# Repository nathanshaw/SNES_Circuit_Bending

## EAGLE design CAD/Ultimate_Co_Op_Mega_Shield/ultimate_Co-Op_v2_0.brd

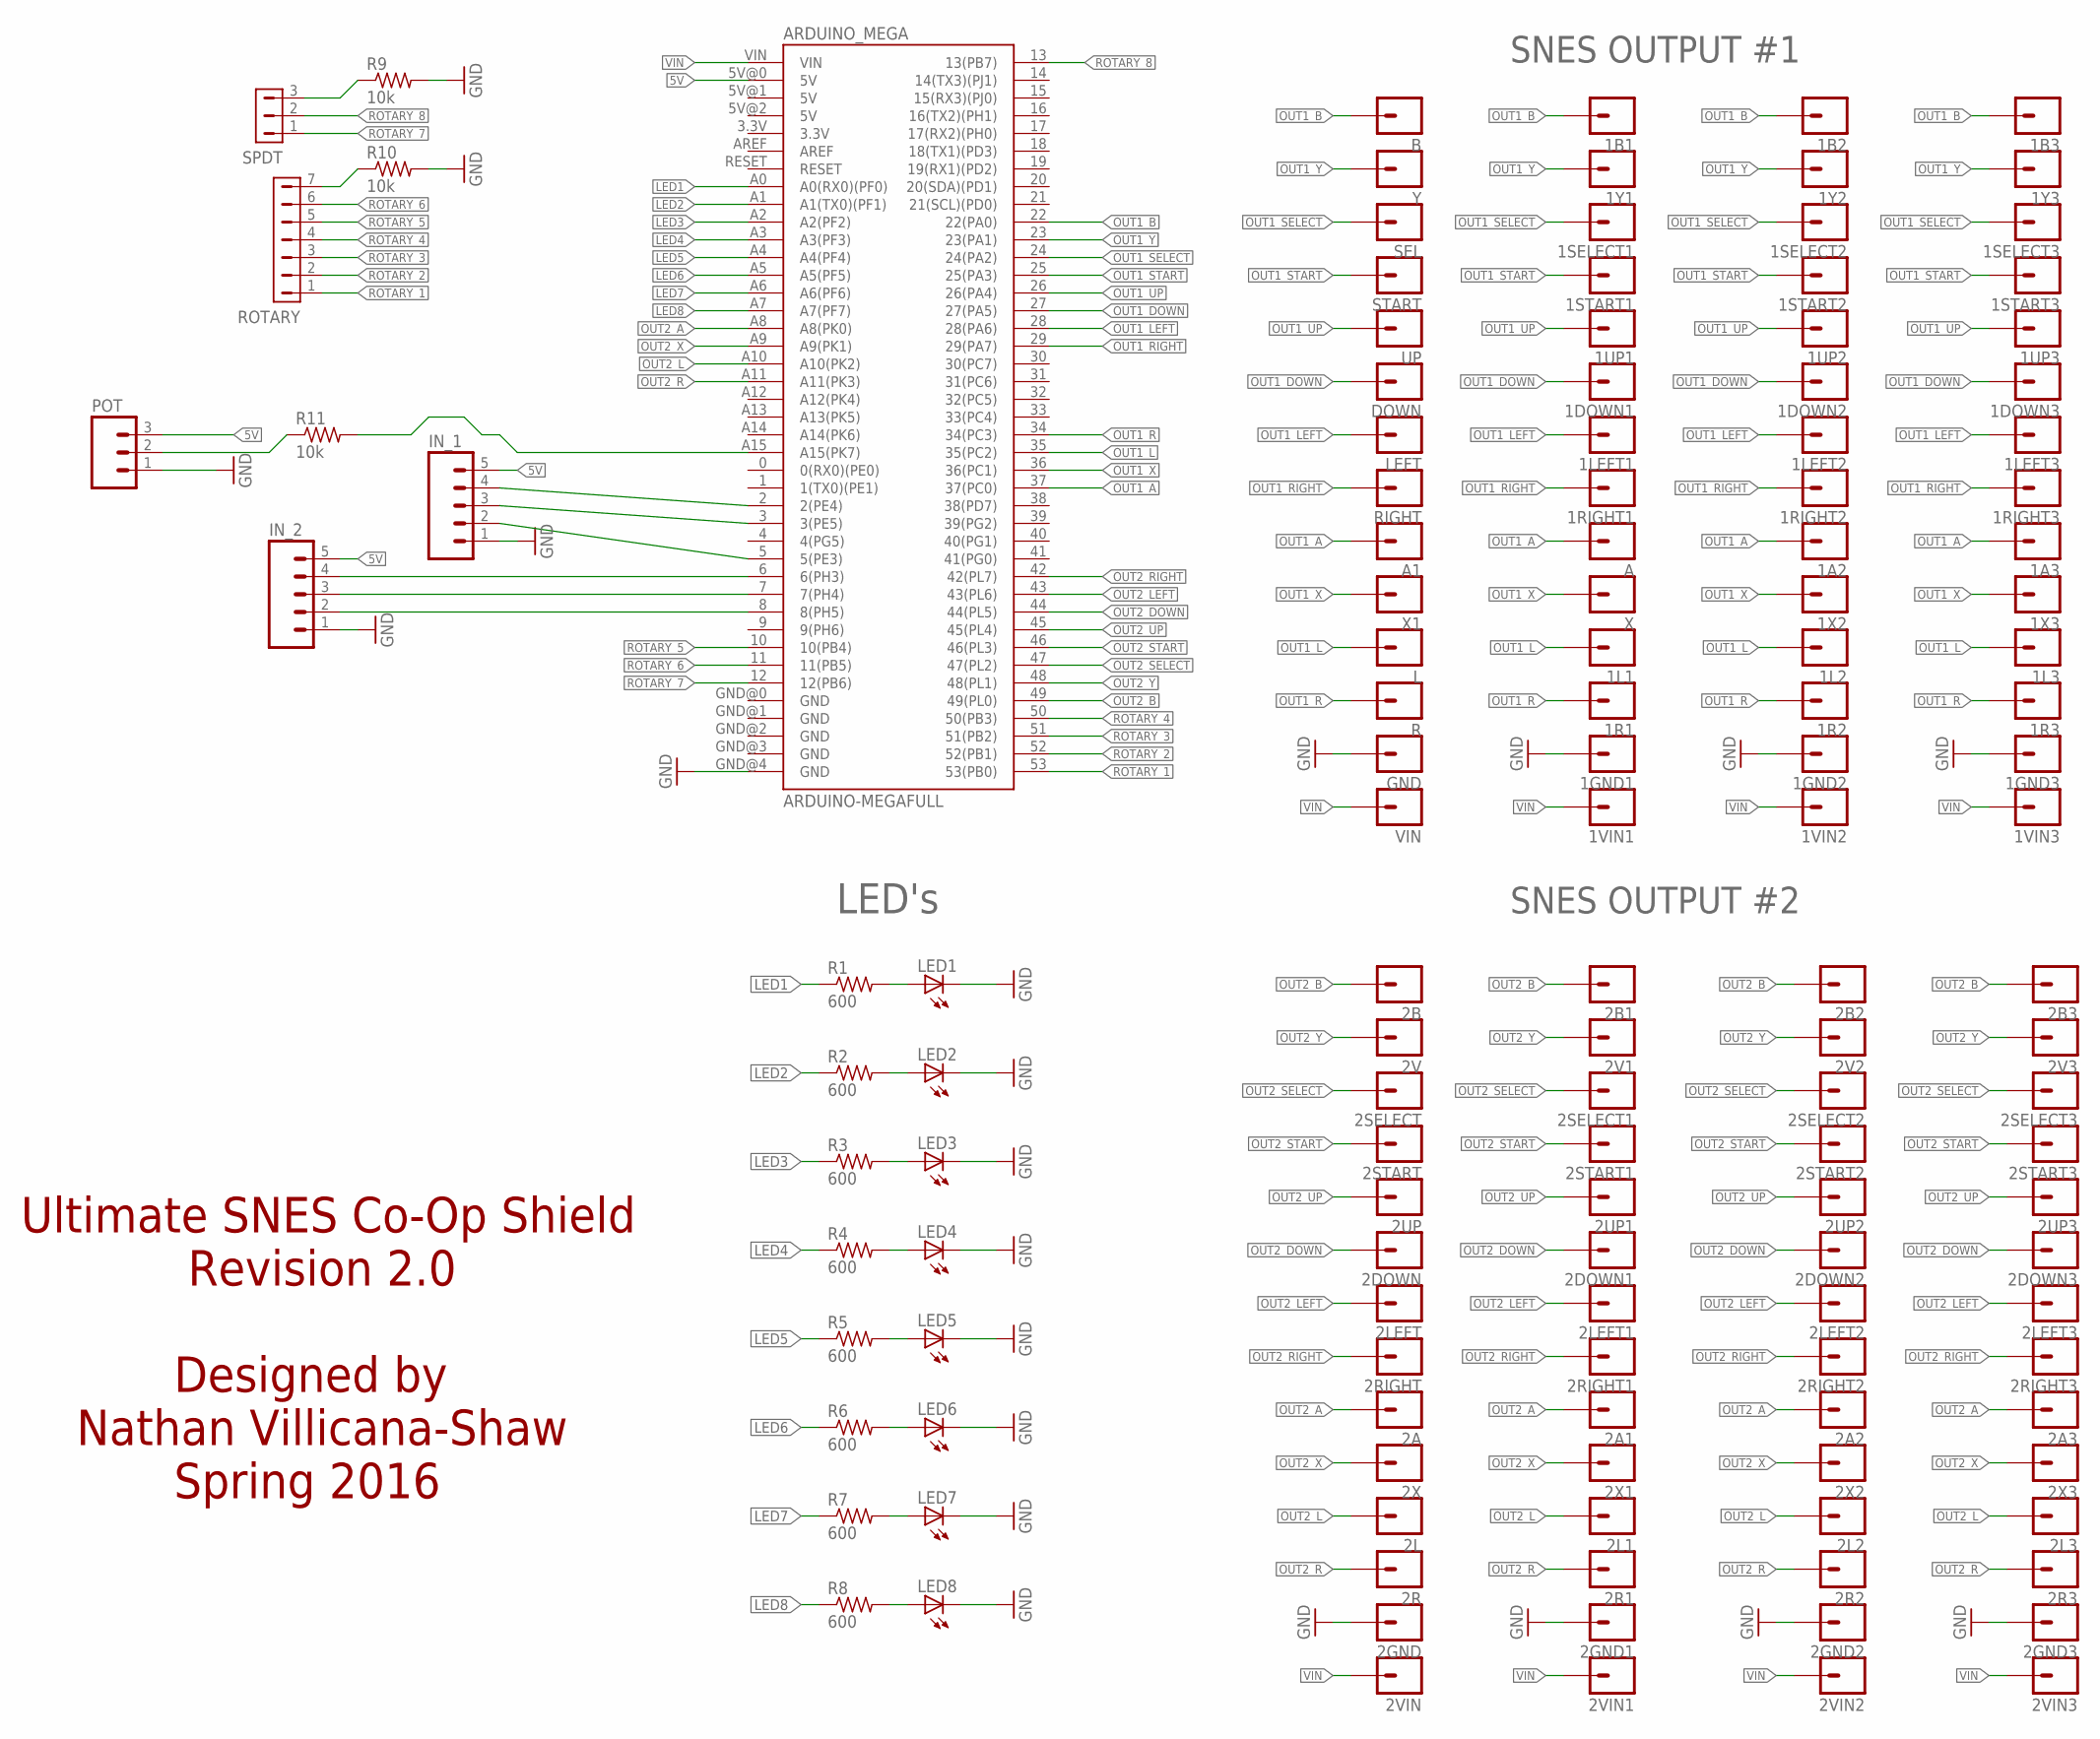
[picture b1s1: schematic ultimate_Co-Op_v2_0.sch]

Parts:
1A2, 1A3, 1B1, 1B2, 1B3, 1DOWN1, 1DOWN2, 1DOWN3, 1GND1, 1GND2, 1GND3, 1L1, 1L2, 1L3, 1LEFT1, 1LEFT2, 1LEFT3, 1R1, 1R2, 1R3, 1RIGHT1, 1RIGHT2, 1RIGHT3, 1SELECT1, 1SELECT2, 1SELECT3, 1START1, 1START2, 1START3, 1UP1, 1UP2, 1UP3, 1VIN1, 1VIN2, 1VIN3, 1X2, 1X3, 1Y1, 1Y2, 1Y3, 2A, 2A1, 2A2, 2A3, 2B, 2B1, 2B2, 2B3, 2DOWN, 2DOWN1, 2DOWN2, 2DOWN3, 2GND, 2GND1, 2GND2, 2GND3, 2L, 2L1, 2L2, 2L3, 2LEFT, 2LEFT1, 2LEFT2, 2LEFT3, 2R, 2R1, 2R2, 2R3, 2RIGHT, 2RIGHT1, 2RIGHT2, 2RIGHT3, 2SELECT, 2SELECT1, 2SELECT2, 2SELECT3, 2START, 2START1, 2START2, 2START3, 2UP, 2UP1, 2UP2, 2UP3, 2V, 2V1, 2V2, 2V3, 2VIN, 2VIN1, 2VIN2, 2VIN3, 2X, 2X1, 2X2, 2X3: M01PTH; 1X01
A, A1: M01PTH; 1X01
ARDUINO_MEGA: ARDUINO-MEGAFULL; ARDUINO_MEGA
B: M01PTH; 1X01
DOWN: M01PTH; 1X01
GND: M01PTH; 1X01
IN_1, IN_2: M05PTH; 1X05
L: M01PTH; 1X01
LED1, LED2, LED3, LED4, LED5, LED6, LED7, LED8: LED5MM
LEFT: M01PTH; 1X01
POT: M03LONGPADS; 1X03_LONGPADS
R: M01PTH; 1X01
R1, R2, R3, R4, R5, R6, R7, R8: 600; 0204/7
R9, R10, R11: 10k; 0204/7
RIGHT: M01PTH; 1X01
ROTARY: HDR-1X7-MTE-100; MTE-100-7V
SEL: M01PTH; 1X01
SPDT: HDR-1X3-MTA-100; MTA-100-3V
START: M01PTH; 1X01
UP: M01PTH; 1X01
VIN: M01PTH; 1X01
X, X1: M01PTH; 1X01
Y: M01PTH; 1X01

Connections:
5V: ARDUINO_MEGA.5V@0 (5V), IN_1.5, IN_2.5, POT.3
GND: 1GND1.1, 1GND2.1, 1GND3.1, 2GND.1, 2GND1.1, 2GND2.1, 2GND3.1, ARDUINO_MEGA.GND@4 (GND), GND.1, IN_1.1, IN_2.1, LED1.K (C), LED2.K (C), LED3.K (C), LED4.K (C), LED5.K (C), LED6.K (C), LED7.K (C), LED8.K (C), POT.1, R9.2, R10.2
LED1: ARDUINO_MEGA.A0 (A0(RX0)(PF0)), R1.1
LED2: ARDUINO_MEGA.A1 (A1(TX0)(PF1)), R2.1
LED3: ARDUINO_MEGA.A2 (A2(PF2)), R3.1
LED4: ARDUINO_MEGA.A3 (A3(PF3)), R4.1
LED5: ARDUINO_MEGA.A4 (A4(PF4)), R5.1
LED6: ARDUINO_MEGA.A5 (A5(PF5)), R6.1
LED7: ARDUINO_MEGA.A6 (A6(PF6)), R7.1
LED8: ARDUINO_MEGA.A7 (A7(PF7)), R8.1
LSJDFKS: ARDUINO_MEGA.6 (6(PH3)), IN_2.4
unnamed: LED1.A, R1.2
unnamed: LED2.A, R2.2
unnamed: LED3.A, R3.2
unnamed: LED4.A, R4.2
unnamed: LED5.A, R5.2
unnamed: LED6.A, R6.2
unnamed: LED7.A, R7.2
unnamed: LED8.A, R8.2
unnamed: ARDUINO_MEGA.2 (2(PE4)), IN_1.4
unnamed: ARDUINO_MEGA.3 (3(PE5)), IN_1.3
unnamed: ARDUINO_MEGA.5 (5(PE3)), IN_1.2
unnamed: ARDUINO_MEGA.A15 (A15(PK7)), R11.2
unnamed: ARDUINO_MEGA.7 (7(PH4)), IN_2.3
unnamed: ARDUINO_MEGA.8 (8(PH5)), IN_2.2
unnamed: POT.2, R11.1
OIJNENLK: R9.1, SPDT.3
OIJNENLK1: R10.1, ROTARY.7
OUT1_A: 1A2.1, 1A3.1, A.1, A1.1, ARDUINO_MEGA.37 (37(PC0))
OUT1_B: 1B1.1, 1B2.1, 1B3.1, ARDUINO_MEGA.22 (22(PA0)), B.1
OUT1_DOWN: 1DOWN1.1, 1DOWN2.1, 1DOWN3.1, ARDUINO_MEGA.27 (27(PA5)), DOWN.1
OUT1_L: 1L1.1, 1L2.1, 1L3.1, ARDUINO_MEGA.35 (35(PC2)), L.1
OUT1_LEFT: 1LEFT1.1, 1LEFT2.1, 1LEFT3.1, ARDUINO_MEGA.28 (28(PA6)), LEFT.1
OUT1_R: 1R1.1, 1R2.1, 1R3.1, ARDUINO_MEGA.34 (34(PC3)), R.1
OUT1_RIGHT: 1RIGHT1.1, 1RIGHT2.1, 1RIGHT3.1, ARDUINO_MEGA.29 (29(PA7)), RIGHT.1
OUT1_SELECT: 1SELECT1.1, 1SELECT2.1, 1SELECT3.1, ARDUINO_MEGA.24 (24(PA2)), SEL.1
OUT1_START: 1START1.1, 1START2.1, 1START3.1, ARDUINO_MEGA.25 (25(PA3)), START.1
OUT1_UP: 1UP1.1, 1UP2.1, 1UP3.1, ARDUINO_MEGA.26 (26(PA4)), UP.1
OUT1_X: 1X2.1, 1X3.1, ARDUINO_MEGA.36 (36(PC1)), X.1, X1.1
OUT1_Y: 1Y1.1, 1Y2.1, 1Y3.1, ARDUINO_MEGA.23 (23(PA1)), Y.1
OUT2_A: 2A.1, 2A1.1, 2A2.1, 2A3.1, ARDUINO_MEGA.A8 (A8(PK0))
OUT2_B: 2B.1, 2B1.1, 2B2.1, 2B3.1, ARDUINO_MEGA.49 (49(PL0))
OUT2_DOWN: 2DOWN.1, 2DOWN1.1, 2DOWN2.1, 2DOWN3.1, ARDUINO_MEGA.44 (44(PL5))
OUT2_L: 2L.1, 2L1.1, 2L2.1, 2L3.1, ARDUINO_MEGA.A10 (A10(PK2))
OUT2_LEFT: 2LEFT.1, 2LEFT1.1, 2LEFT2.1, 2LEFT3.1, ARDUINO_MEGA.43 (43(PL6))
OUT2_R: 2R.1, 2R1.1, 2R2.1, 2R3.1, ARDUINO_MEGA.A11 (A11(PK3))
OUT2_RIGHT: 2RIGHT.1, 2RIGHT1.1, 2RIGHT2.1, 2RIGHT3.1, ARDUINO_MEGA.42 (42(PL7))
OUT2_SELECT: 2SELECT.1, 2SELECT1.1, 2SELECT2.1, 2SELECT3.1, ARDUINO_MEGA.47 (47(PL2))
OUT2_START: 2START.1, 2START1.1, 2START2.1, 2START3.1, ARDUINO_MEGA.46 (46(PL3))
OUT2_UP: 2UP.1, 2UP1.1, 2UP2.1, 2UP3.1, ARDUINO_MEGA.45 (45(PL4))
OUT2_X: 2X.1, 2X1.1, 2X2.1, 2X3.1, ARDUINO_MEGA.A9 (A9(PK1))
OUT2_Y: 2V.1, 2V1.1, 2V2.1, 2V3.1, ARDUINO_MEGA.48 (48(PL1))
ROTARY_1: ARDUINO_MEGA.53 (53(PB0)), ROTARY.1
ROTARY_2: ARDUINO_MEGA.52 (52(PB1)), ROTARY.2
ROTARY_3: ARDUINO_MEGA.51 (51(PB2)), ROTARY.3
ROTARY_4: ARDUINO_MEGA.50 (50(PB3)), ROTARY.4
ROTARY_5: ARDUINO_MEGA.10 (10(PB4)), ROTARY.5
ROTARY_6: ARDUINO_MEGA.11 (11(PB5)), ROTARY.6
ROTARY_7: ARDUINO_MEGA.12 (12(PB6)), SPDT.1
ROTARY_8: ARDUINO_MEGA.13 (13(PB7)), SPDT.2
VIN: 1VIN1.1, 1VIN2.1, 1VIN3.1, 2VIN.1, 2VIN1.1, 2VIN2.1, 2VIN3.1, ARDUINO_MEGA.VIN, VIN.1

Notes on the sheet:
LED's
SNES OUTPUT #1
SNES OUTPUT #2
Ultimate SNES Co-Op Shield Revision 2.0 Designed by Nathan Villicana-Shaw Spring 2016

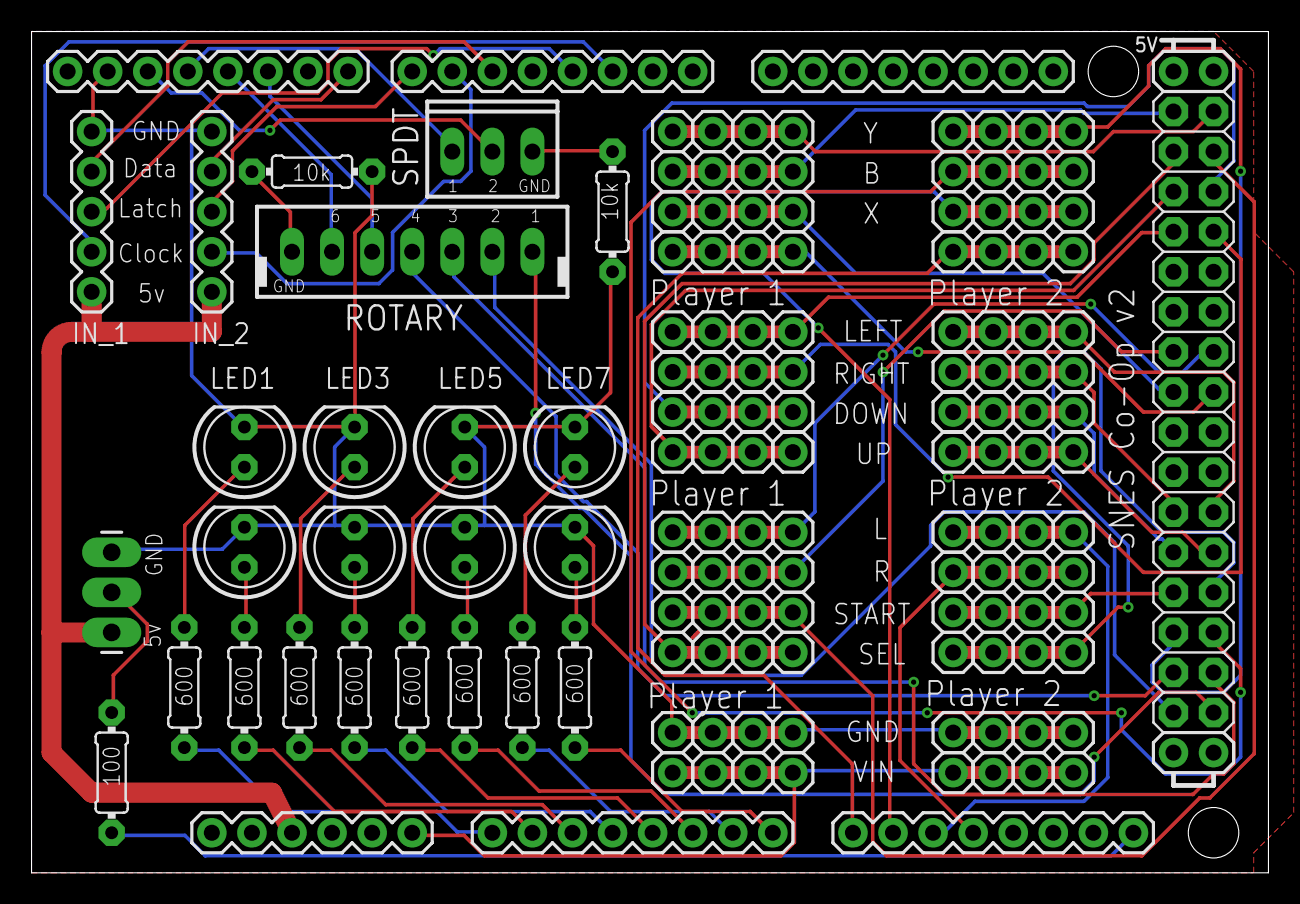
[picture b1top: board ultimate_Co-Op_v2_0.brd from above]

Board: 2 copper layers, 78.4 x 53.3 mm, 137 parts (0 on the bottom side), 61 nets.

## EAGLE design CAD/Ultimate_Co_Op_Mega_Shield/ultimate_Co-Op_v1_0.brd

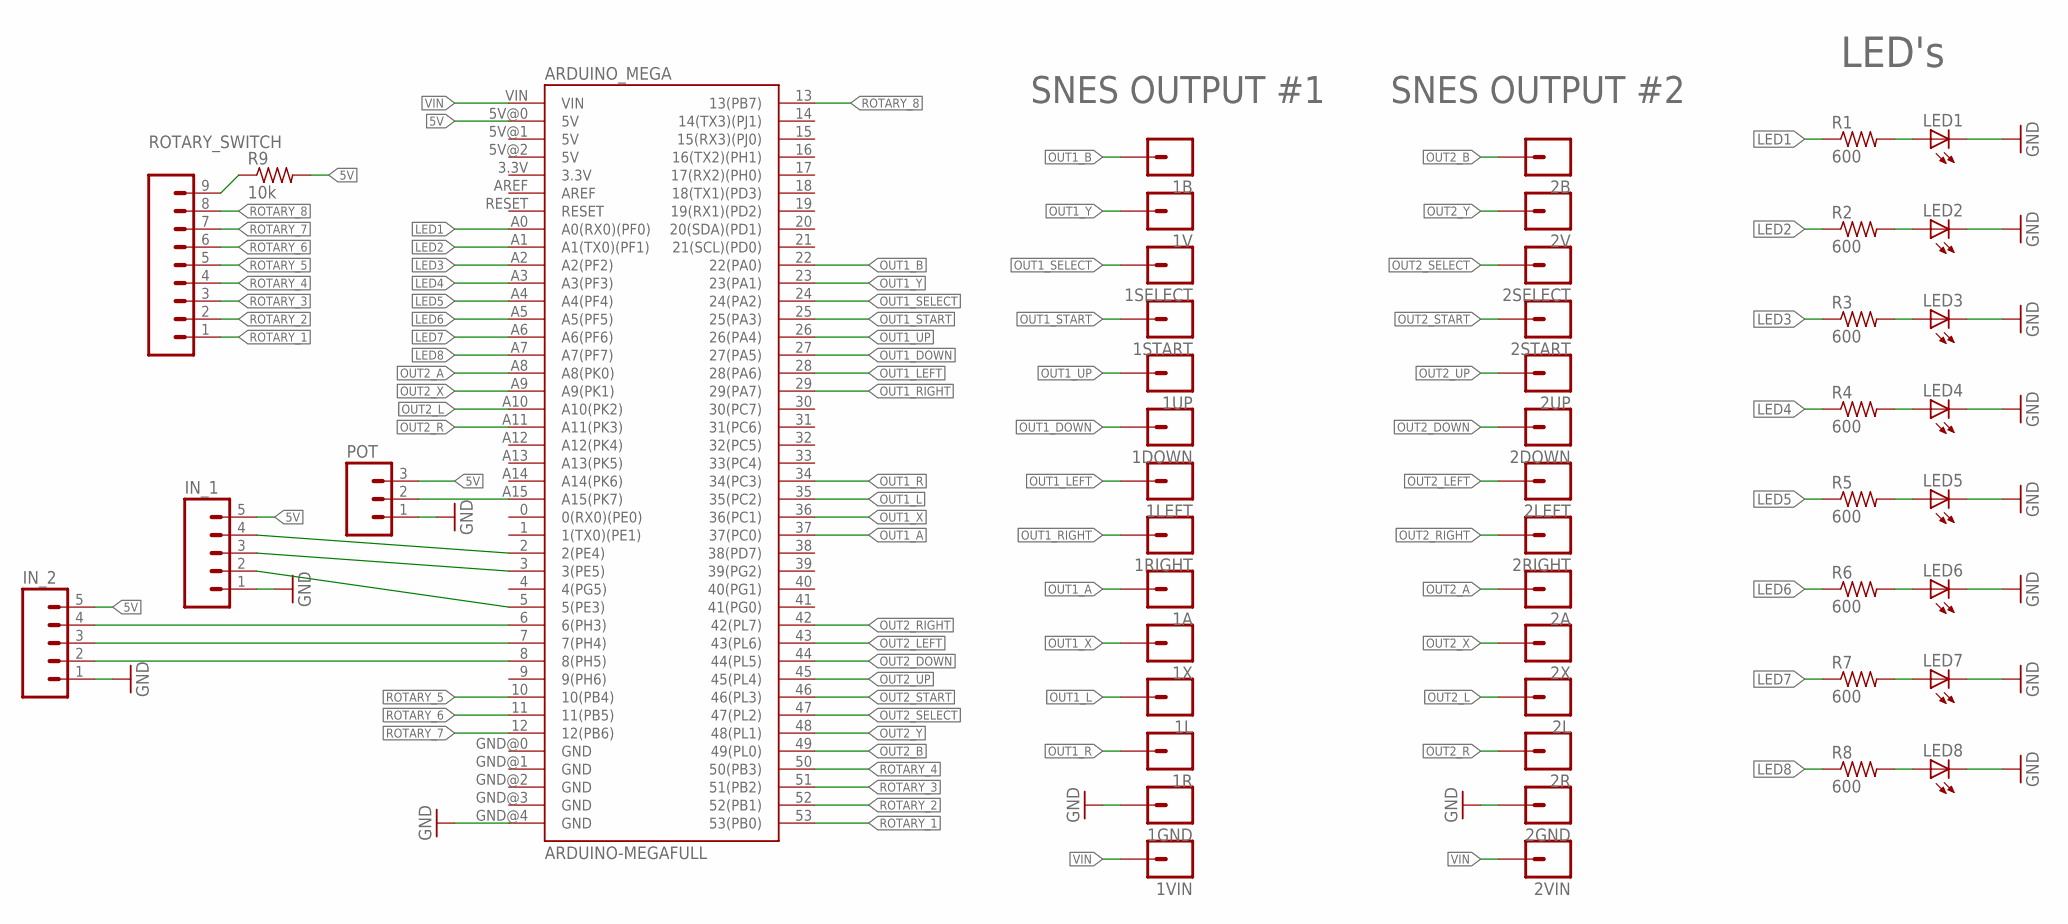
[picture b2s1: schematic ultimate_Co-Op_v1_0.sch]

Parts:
1A, 1B, 1DOWN, 1GND, 1L, 1LEFT, 1R, 1RIGHT, 1SELECT, 1START, 1UP, 1V, 1VIN, 1X, 2A, 2B, 2DOWN, 2GND, 2L, 2LEFT, 2R, 2RIGHT, 2SELECT, 2START, 2UP, 2V, 2VIN, 2X: M01PTH; 1X01
ARDUINO_MEGA: ARDUINO-MEGAFULL; ARDUINO_MEGA
IN_1, IN_2: M05PTH; 1X05
LED1, LED2, LED3, LED4, LED5, LED6, LED7, LED8: LED5MM
POT: M03LONGPADS; 1X03_LONGPADS
R1, R2, R3, R4, R5, R6, R7, R8: 600; 0204/7
R9: 10k; 0204/7
ROTARY_SWITCH: M09; 1X09

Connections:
5V: ARDUINO_MEGA.5V@0 (5V), IN_1.5, IN_2.5, POT.3, R9.2
GND: 1GND.1, 2GND.1, ARDUINO_MEGA.GND@4 (GND), IN_1.1, IN_2.1, LED1.K (C), LED2.K (C), LED3.K (C), LED4.K (C), LED5.K (C), LED6.K (C), LED7.K (C), LED8.K (C), POT.1
LED1: ARDUINO_MEGA.A0 (A0(RX0)(PF0)), R1.1
LED2: ARDUINO_MEGA.A1 (A1(TX0)(PF1)), R2.1
LED3: ARDUINO_MEGA.A2 (A2(PF2)), R3.1
LED4: ARDUINO_MEGA.A3 (A3(PF3)), R4.1
LED5: ARDUINO_MEGA.A4 (A4(PF4)), R5.1
LED6: ARDUINO_MEGA.A5 (A5(PF5)), R6.1
LED7: ARDUINO_MEGA.A6 (A6(PF6)), R7.1
LED8: ARDUINO_MEGA.A7 (A7(PF7)), R8.1
LSJDFKS: ARDUINO_MEGA.6 (6(PH3)), IN_2.4
unnamed: LED1.A, R1.2
unnamed: LED2.A, R2.2
unnamed: LED3.A, R3.2
unnamed: LED4.A, R4.2
unnamed: LED5.A, R5.2
unnamed: LED6.A, R6.2
unnamed: LED7.A, R7.2
unnamed: LED8.A, R8.2
unnamed: ARDUINO_MEGA.2 (2(PE4)), IN_1.4
unnamed: ARDUINO_MEGA.3 (3(PE5)), IN_1.3
unnamed: ARDUINO_MEGA.5 (5(PE3)), IN_1.2
unnamed: ARDUINO_MEGA.7 (7(PH4)), IN_2.3
unnamed: ARDUINO_MEGA.8 (8(PH5)), IN_2.2
OIJNENLK: R9.1, ROTARY_SWITCH.9
OUT1_A: 1A.1, ARDUINO_MEGA.37 (37(PC0))
OUT1_B: 1B.1, ARDUINO_MEGA.22 (22(PA0))
OUT1_DOWN: 1DOWN.1, ARDUINO_MEGA.27 (27(PA5))
OUT1_L: 1L.1, ARDUINO_MEGA.35 (35(PC2))
OUT1_LEFT: 1LEFT.1, ARDUINO_MEGA.28 (28(PA6))
OUT1_R: 1R.1, ARDUINO_MEGA.34 (34(PC3))
OUT1_RIGHT: 1RIGHT.1, ARDUINO_MEGA.29 (29(PA7))
OUT1_SELECT: 1SELECT.1, ARDUINO_MEGA.24 (24(PA2))
OUT1_START: 1START.1, ARDUINO_MEGA.25 (25(PA3))
OUT1_UP: 1UP.1, ARDUINO_MEGA.26 (26(PA4))
OUT1_X: 1X.1, ARDUINO_MEGA.36 (36(PC1))
OUT1_Y: 1V.1, ARDUINO_MEGA.23 (23(PA1))
OUT2_A: 2A.1, ARDUINO_MEGA.A8 (A8(PK0))
OUT2_B: 2B.1, ARDUINO_MEGA.49 (49(PL0))
OUT2_DOWN: 2DOWN.1, ARDUINO_MEGA.44 (44(PL5))
OUT2_L: 2L.1, ARDUINO_MEGA.A10 (A10(PK2))
OUT2_LEFT: 2LEFT.1, ARDUINO_MEGA.43 (43(PL6))
OUT2_R: 2R.1, ARDUINO_MEGA.A11 (A11(PK3))
OUT2_RIGHT: 2RIGHT.1, ARDUINO_MEGA.42 (42(PL7))
OUT2_SELECT: 2SELECT.1, ARDUINO_MEGA.47 (47(PL2))
OUT2_START: 2START.1, ARDUINO_MEGA.46 (46(PL3))
OUT2_UP: 2UP.1, ARDUINO_MEGA.45 (45(PL4))
OUT2_X: 2X.1, ARDUINO_MEGA.A9 (A9(PK1))
OUT2_Y: 2V.1, ARDUINO_MEGA.48 (48(PL1))
POT1: ARDUINO_MEGA.A15 (A15(PK7)), POT.2
ROTARY_1: ARDUINO_MEGA.53 (53(PB0)), ROTARY_SWITCH.1
ROTARY_2: ARDUINO_MEGA.52 (52(PB1)), ROTARY_SWITCH.2
ROTARY_3: ARDUINO_MEGA.51 (51(PB2)), ROTARY_SWITCH.3
ROTARY_4: ARDUINO_MEGA.50 (50(PB3)), ROTARY_SWITCH.4
ROTARY_5: ARDUINO_MEGA.10 (10(PB4)), ROTARY_SWITCH.5
ROTARY_6: ARDUINO_MEGA.11 (11(PB5)), ROTARY_SWITCH.6
ROTARY_7: ARDUINO_MEGA.12 (12(PB6)), ROTARY_SWITCH.7
ROTARY_8: ARDUINO_MEGA.13 (13(PB7)), ROTARY_SWITCH.8
VIN: 1VIN.1, 2VIN.1, ARDUINO_MEGA.VIN

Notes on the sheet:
LED's
SNES OUTPUT #1
SNES OUTPUT #2

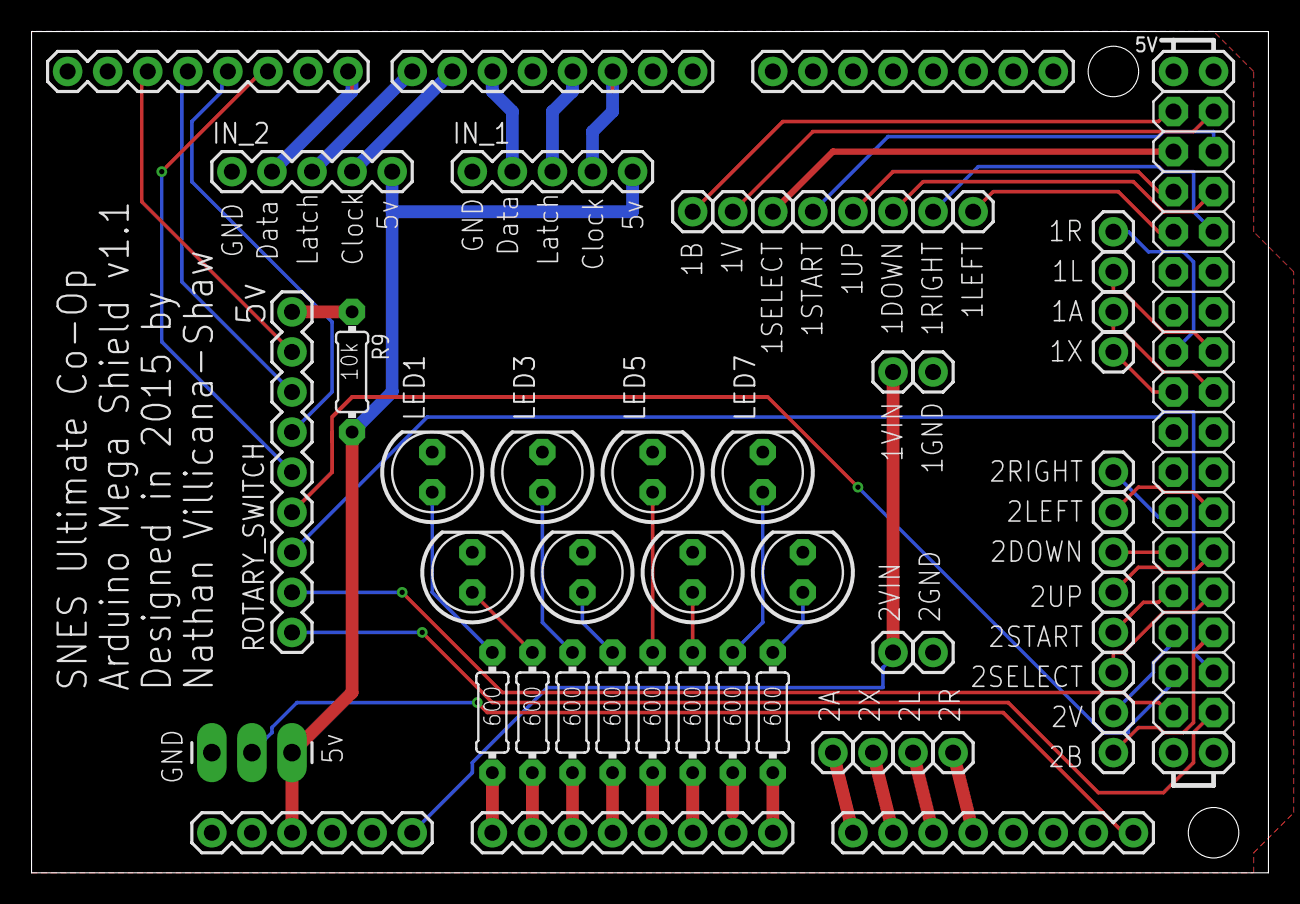
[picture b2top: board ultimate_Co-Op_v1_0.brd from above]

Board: 2 copper layers, 78.4 x 53.3 mm, 50 parts (0 on the bottom side), 59 nets.

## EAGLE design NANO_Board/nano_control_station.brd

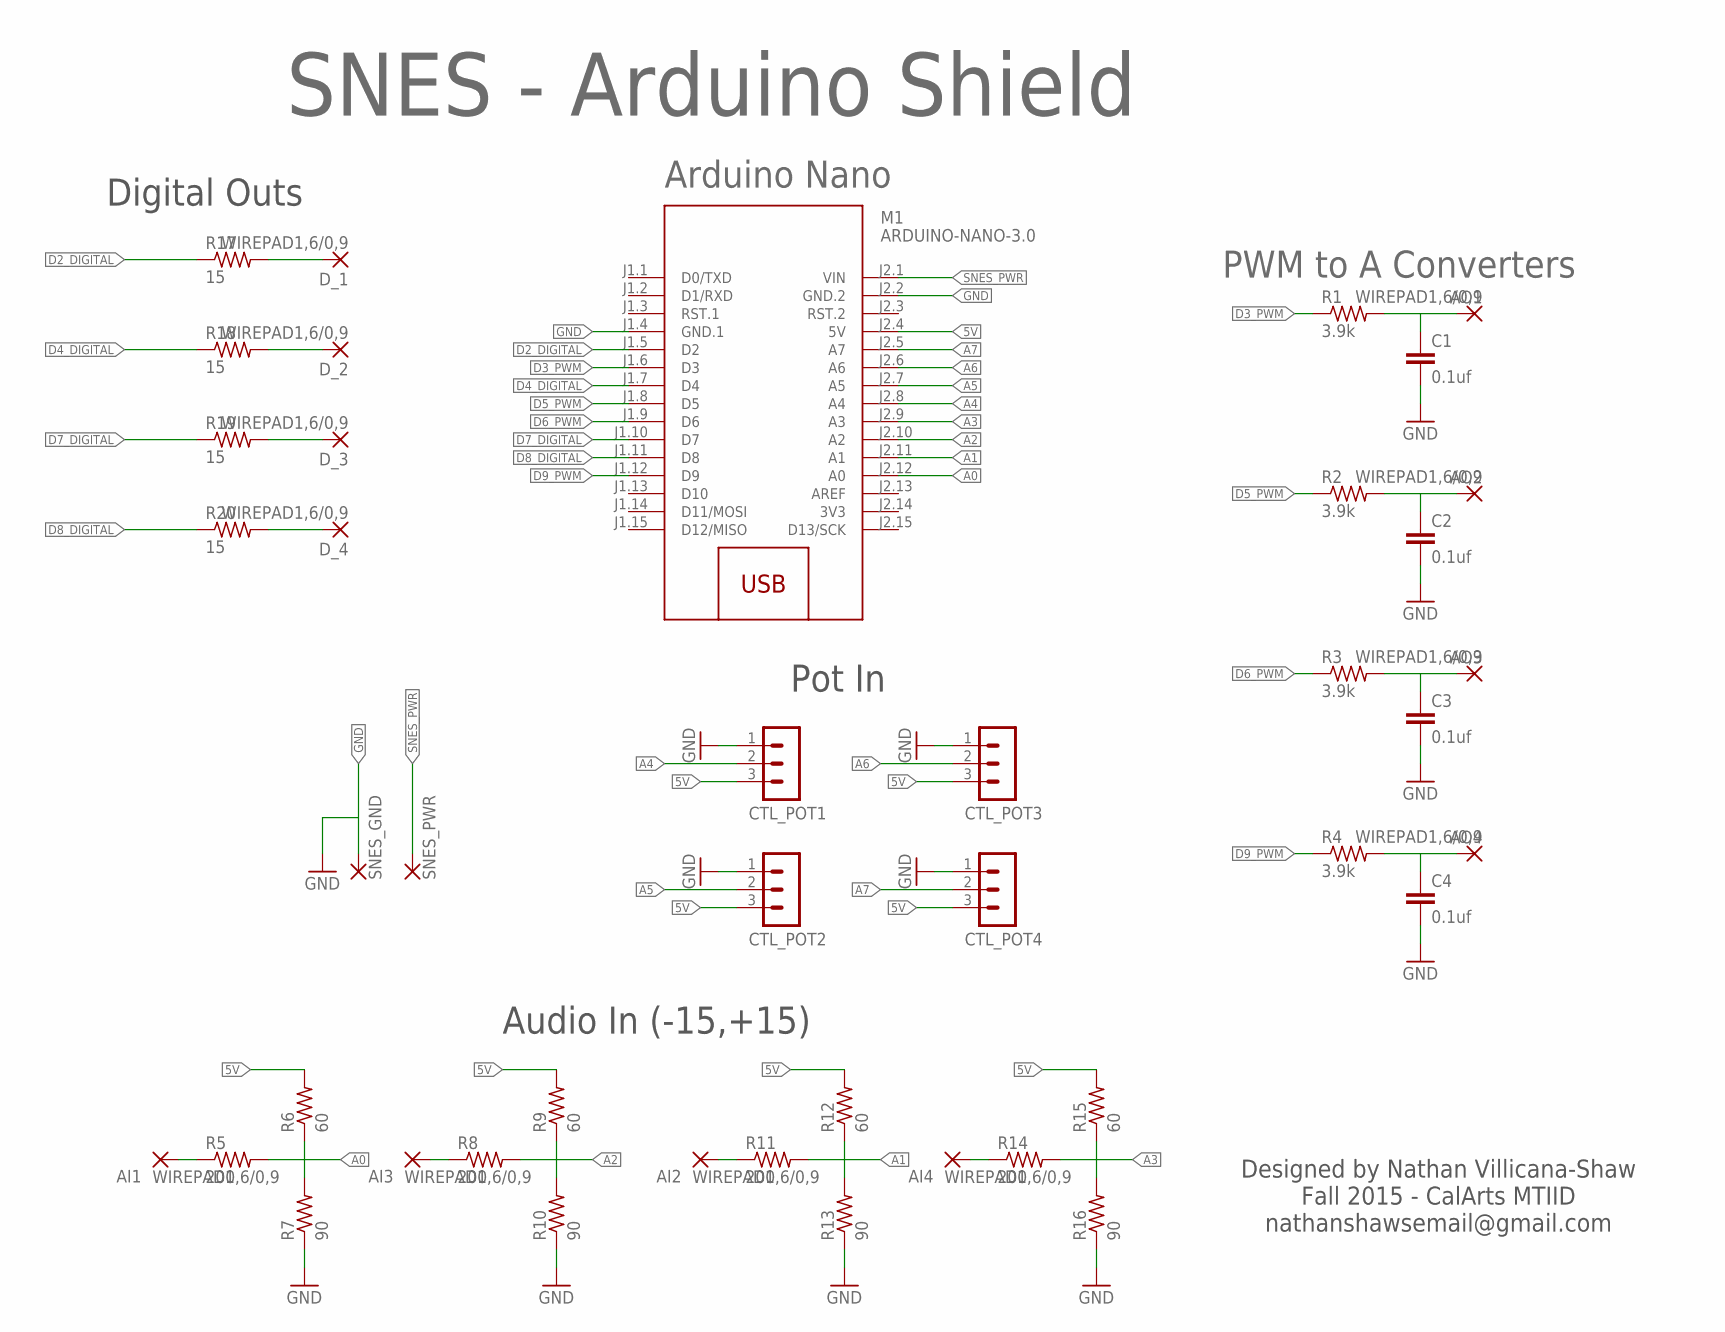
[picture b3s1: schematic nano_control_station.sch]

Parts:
AI1, AI2, AI3, AI4: WIREPAD1,6/0,9; 1,6/0,9
AO1, AO2, AO3, AO4: WIREPAD1,6/0,9; 1,6/0,9
C1, C2, C3, C4: 0.1uf; C2.5-2
CTL_POT1, CTL_POT2, CTL_POT3, CTL_POT4: MA03-1
D_1, D_2, D_3, D_4: WIREPAD1,6/0,9; 1,6/0,9
M1: ARDUINO-NANO-3.0
R1, R2, R3, R4: 3.9k; 0204/7
R5, R8, R11, R14: 200; 0204/7
R6, R9, R12, R15: 60; 0204/7
R7, R10, R13, R16: 90; 0204/7
R17, R18, R19, R20: 15; 0204/7
SNES_GND: 2,15/1,0
SNES_PWR: 2,15/1,0

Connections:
3V3: M1.J2.14 (3V3)
5V: CTL_POT1.3, CTL_POT2.3, CTL_POT3.3, CTL_POT4.3, M1.J2.4 (5V), R6.2, R9.2, R12.2, R15.2
A0: M1.J2.12 (A0), R5.2, R6.1, R7.2
A1: M1.J2.11 (A1), R11.2, R12.1, R13.2
A2: M1.J2.10 (A2), R8.2, R9.1, R10.2
A3: M1.J2.9 (A3), R14.2, R15.1, R16.2
A4: CTL_POT1.2, M1.J2.8 (A4)
A5: CTL_POT2.2, M1.J2.7 (A5)
A6: CTL_POT3.2, M1.J2.6 (A6)
A7: CTL_POT4.2, M1.J2.5 (A7)
D2_DIGITAL: M1.J1.5 (D2), R17.1
D3_PWM: M1.J1.6 (D3), R1.1
D4_DIGITAL: M1.J1.7 (D4), R18.1
D5_PWM: M1.J1.8 (D5), R2.1
D6_PWM: M1.J1.9 (D6), R3.1
D7_DIGITAL: M1.J1.10 (D7), R19.1
D8_DIGITAL: M1.J1.11 (D8), R20.1
D9_PWM: M1.J1.12 (D9), R4.1
GND: C1.2, C2.2, C3.2, C4.2, CTL_POT1.1, CTL_POT2.1, CTL_POT3.1, CTL_POT4.1, M1.J1.4 (GND.1), M1.J2.2 (GND.2), R7.1, R10.1, R13.1, R16.1, SNES_GND.1
unnamed: AI3.1, R8.1
unnamed: AO1.1, C1.1, R1.2
unnamed: AO2.1, C2.1, R2.2
unnamed: AO3.1, C3.1, R3.2
unnamed: AO4.1, C4.1, R4.2
unnamed: AI1.1, R5.1
unnamed: AI2.1, R11.1
unnamed: AI4.1, R14.1
unnamed: D_2.1, R18.2
unnamed: D_1.1, R17.2
unnamed: D_3.1, R19.2
unnamed: D_4.1, R20.2
SNES_PWR: M1.J2.1 (VIN), SNES_PWR.1

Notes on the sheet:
PWM to A Converters
Audio In (-15,+15)
Digital Outs
Pot In
Arduino Nano
SNES - Arduino Shield
Designed by Nathan Villicana-Shaw Fall 2015 - CalArts MTIID nathanshawsemail@gmail.com

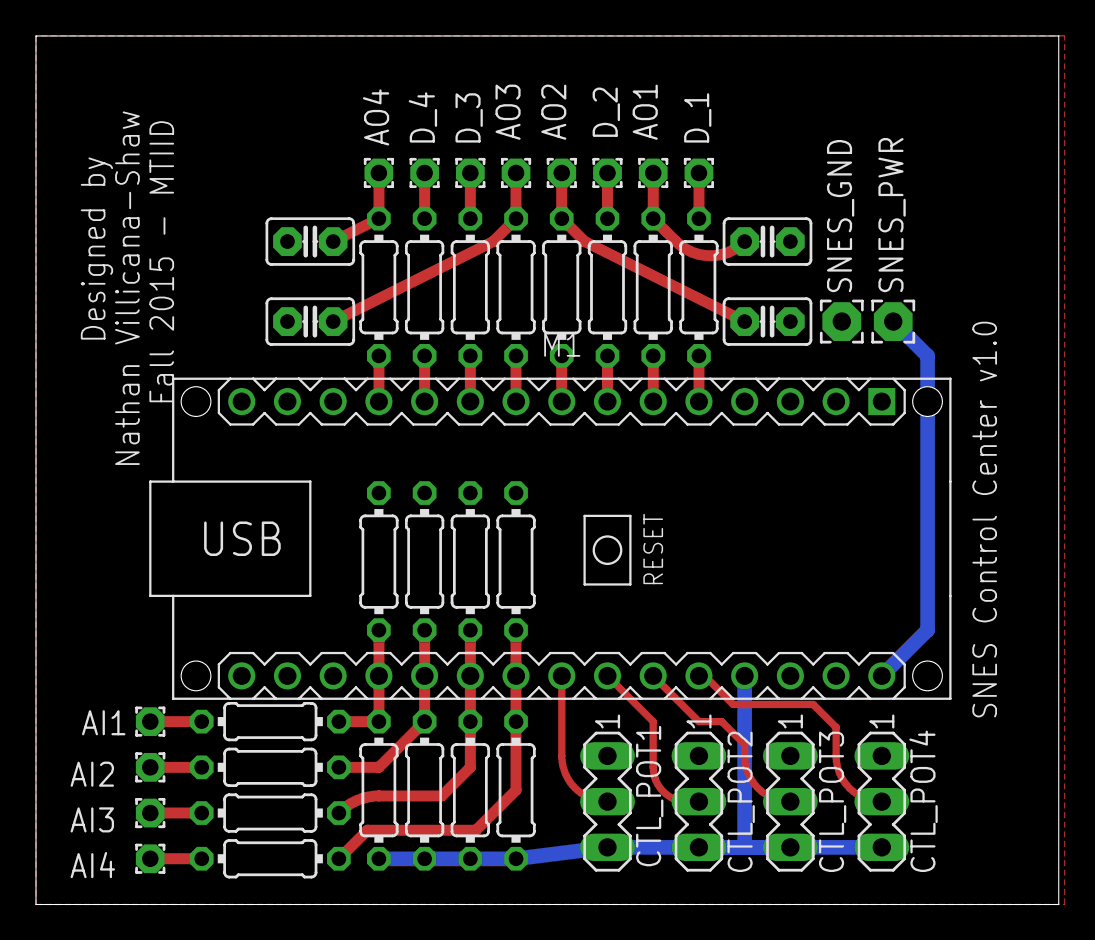
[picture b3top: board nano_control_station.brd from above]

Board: 2 copper layers, 56.8 x 48.2 mm, 43 parts (0 on the bottom side), 31 nets.

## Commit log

2015-11-13 initial commit, eagle boards and arduino code
2015-11-13 updated gitignore
2015-12-06 added sketch for converting two controller inputs into one input screen, still needs to output data but is receiving fine
2015-12-06 added support for slower alternation between the two players, overloaded several methods to deal with both ints and bytes for allow for NES and SNES support?
2015-12-07 moving along, one bit at a time, hahahahahahHA
2015-12-07 rough, working version ready for testing
2015-12-08 cleaned some things up, added a PLAYERS_DIFFER mode that utalizes an x-or
2015-12-09 added new file for a sabotage version that has two output controllers
2015-12-10 added second output controller
2015-12-16 added more defines for port names for readability, created player 1 and player 2 variables for current and past output data.
2015-12-17 added dprint and dprintln functions for debug printing to try and clean things up
2015-12-18 added eagle files for ultimate co-op arduino mega shield
2016-01-05 new version of the board for the SNES that accounts for the five pins on the controllers and a a few other minor other mistakes
2016-01-06 created a 'mini' version of the co-op board
2016-01-06 created a 'mini' version of the co-op board again...
2016-01-09 added folder for keeping track of invoices related to project and created code for the 1 to 4 project
2016-01-12 made changes to the gitignore file
2016-01-12 removed invoices
2016-01-17 added git ignore file to project
2016-01-17 renamed firmware to make more sense, wrote extended multiplayer code for the second version of the shield
2016-01-17 removed redundent copies of projects
2016-01-17 reworked LED code a little and started expanding on the shield
2016-01-18 added gitignore to my gitignore =)
2016-01-18 added snes schematic to the repo
2016-01-24 a few minor changes to the board, now has one rotaty and one switch
2016-01-30 added simplified version of the firmware for oneTofour
2016-01-31 added a version of the sketch for hardware control only (only using the rotary knob with no software mode control)
2016-02-03 added updates to the ultimate co-op shield
2016-02-03 updated the firmware for the various projects
2016-02-05 added POC code for the automatic switcher
2016-02-06 several updates to the firmware
2016-02-11 a few changes to hardware control only, moving some things around
2016-02-21 started reworking the modular SNES code
2016-02-22 updated the modular SNES firmware so it actually works
2016-02-22 final changes to hardware_control only
2016-02-24 added better multiplayer modes, got rid of players diverge, added normal modes, added counting of button presses
2016-02-24 flushed out the teamwork mode at long last
2016-02-25 jennings lesson
2016-02-26 removed uneeded variables and functions from the oneTwoFour code
2016-02-26 removed two old projects that are no longer current
2016-02-27 some minor clean ups for the oneTwoFour code
2016-02-27 changed the names of the firmware projects
2016-02-27 renamed modular snes shield file
2016-02-29 started modularizing the code for ultimate coop
2016-02-29 moved printing out of the modular SNES main code
2016-04-10 started on code for a single mode version of the ultimate co-op project
2016-04-11 got basic version finished
2016-04-11 needs testing, took out delay statements
2016-04-22 finalized version of the single mode snes synergy firmware
2016-05-24 added keynote presentation to the repo
2017-01-26 added picture to readme

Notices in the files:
parts and their libraries:
SparkFun-Connectors: Licensing: Creative Commons ShareAlike 4.0 International - https://creativecommons.org/licenses/by-sa/4.0
con-hdrs40: Copyright (C) 2004, Bob Starr (bobstarr@mindspring.com)
